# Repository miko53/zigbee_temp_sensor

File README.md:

# zigbee temperature sensor

This repository contains project about a temperature sensor based on Xbee device.
It will be coupled with the zigbee controler and the web_monitoring projets to resp. retrieve the value from the sensor 
and display thought a web site.

## Hardware part
The hardware folder groups schematics. it is based on a PIC device (PIC18LF2420) coupled with a XBee module (from Digi)
Temperature and Humidity sensor is a HYT221

## Firmware part
The folder contains source code to build the firmware for the PIC device.

## Features
 - read temperature and humidity around each minutes
 - read the battery voltage
 - PIC clock calibration
Most of 
 
##### Note:
 - acquisition period will be reviewed to improve consumption
 
autonomy test on going, with hourly reception of battery value and reception of temp/humidity each minutes
 - estimation: more than 6 months if I interpolate the current consumption.

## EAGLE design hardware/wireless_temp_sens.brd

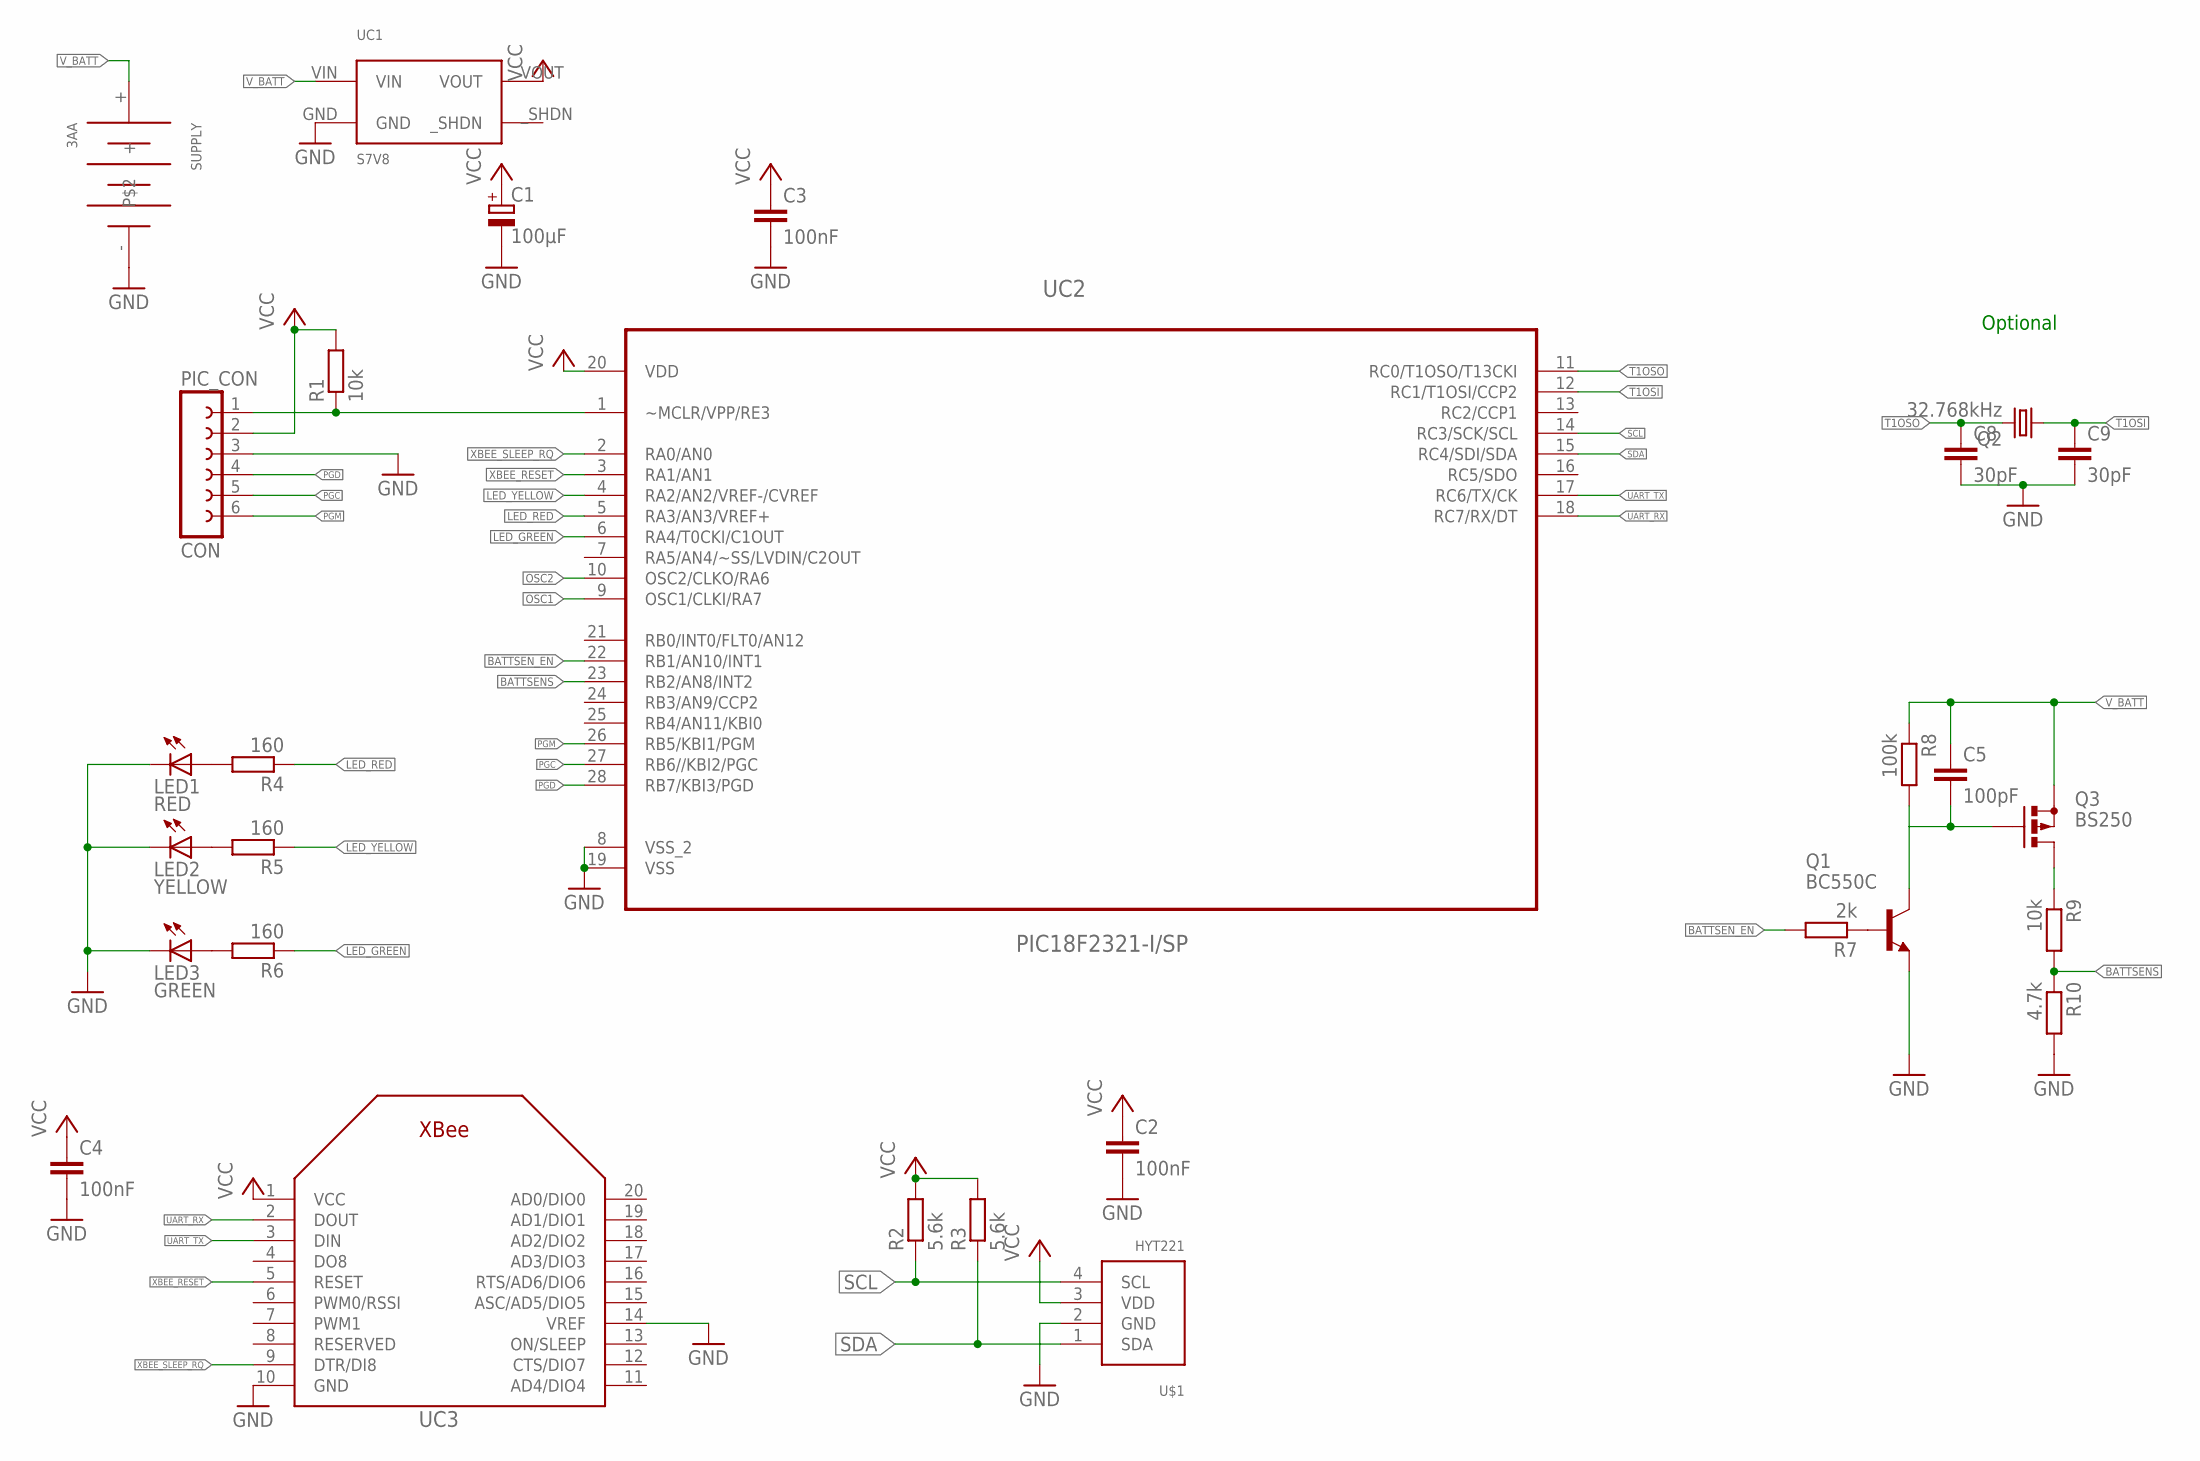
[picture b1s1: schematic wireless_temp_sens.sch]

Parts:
C1: 100µF; E2,5-6
C2, C3, C4: 100nF; C025-025X050
C5: 100pF; C025-025X050
C8, C9: 30pF; C025-024X044
CON: PIC_CON; FE06
LED1: RED; LED3MM
LED2: YELLOW; LED3MM
LED3: GREEN; LED3MM
Q1: BC550C; TO92-EBC
Q2: 32.768kHz; TC26H
Q3: BS250; SOT54E
R1, R9: 10k; 0204/7
R2, R3: 5.6k; 0204/7
R4, R5, R6: 160; 0204/7
R7: 2k; 0204/7
R8: 100k; 0204/7
R10: 4.7k; 0204/7
SUPPLY: 3AA; LR6-R6-R6P
U$1: HYT221HYT221-CON; HYT221-CON
UC1: S7V8; S7V8_P
UC2: PIC18F2321-I/SP; DIP254P762X508-28
UC3: XBEE

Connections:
BATTSENS: R9.2, R10.1, UC2.23 (RB2/AN8/INT2)
BATTSEN_EN: R7.2, UC2.22 (RB1/AN10/INT1)
GND: C1.-, C2.2, C3.2, C4.2, C8.2, C9.2, CON.3, LED1.K (C), LED2.K (C), LED3.K (C), Q1.E, R10.2, SUPPLY.-, U$1.2 (GND), UC1.GND, UC2.8 (VSS_2), UC2.19 (VSS), UC3.10 (GND), UC3.14 (VREF)
LED_GREEN: R6.1, UC2.6 (RA4/T0CKI/C1OUT)
LED_RED: R4.1, UC2.5 (RA3/AN3/VREF+)
LED_YELLOW: R5.1, UC2.4 (RA2/AN2/VREF-/CVREF)
unnamed: Q1.B, R7.1
unnamed: CON.1, R1.1, UC2.1 (~MCLR/VPP/RE3)
unnamed: Q3.D, R9.1
unnamed: C5.2, Q1.C, Q3.G, R8.2
unnamed: LED1.A, R4.2
unnamed: LED2.A, R5.2
unnamed: LED3.A, R6.2
OSC1: UC2.9 (OSC1/CLKI/RA7)
OSC2: UC2.10 (OSC2/CLKO/RA6)
PGC: CON.5, UC2.27 (RB6//KBI2/PGC)
PGD: CON.4, UC2.28 (RB7/KBI3/PGD)
PGM: CON.6, UC2.26 (RB5/KBI1/PGM)
SCL: R2.1, U$1.4 (SCL), UC2.14 (RC3/SCK/SCL)
SDA: R3.1, U$1.1 (SDA), UC2.15 (RC4/SDI/SDA)
T1OSI: C9.1, Q2.1, UC2.12 (RC1/T1OSI/CCP2)
T1OSO: C8.1, Q2.2, UC2.11 (RC0/T1OSO/T13CKI)
UART_RX: UC2.18 (RC7/RX/DT), UC3.2 (DOUT)
UART_TX: UC2.17 (RC6/TX/CK), UC3.3 (DIN)
VCC: C1.+, C2.1, C3.1, C4.1, CON.2, R1.2, R2.2, R3.2, U$1.3 (VDD), UC1.VOUT, UC2.20 (VDD), UC3.1 (VCC)
V_BATT: C5.1, Q3.S, R8.1, SUPPLY.+, UC1.VIN
XBEE_RESET: UC2.3 (RA1/AN1), UC3.5 (RESET)
XBEE_SLEEP_RQ: UC2.2 (RA0/AN0), UC3.9 (DTR/DI8)

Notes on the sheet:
Optional

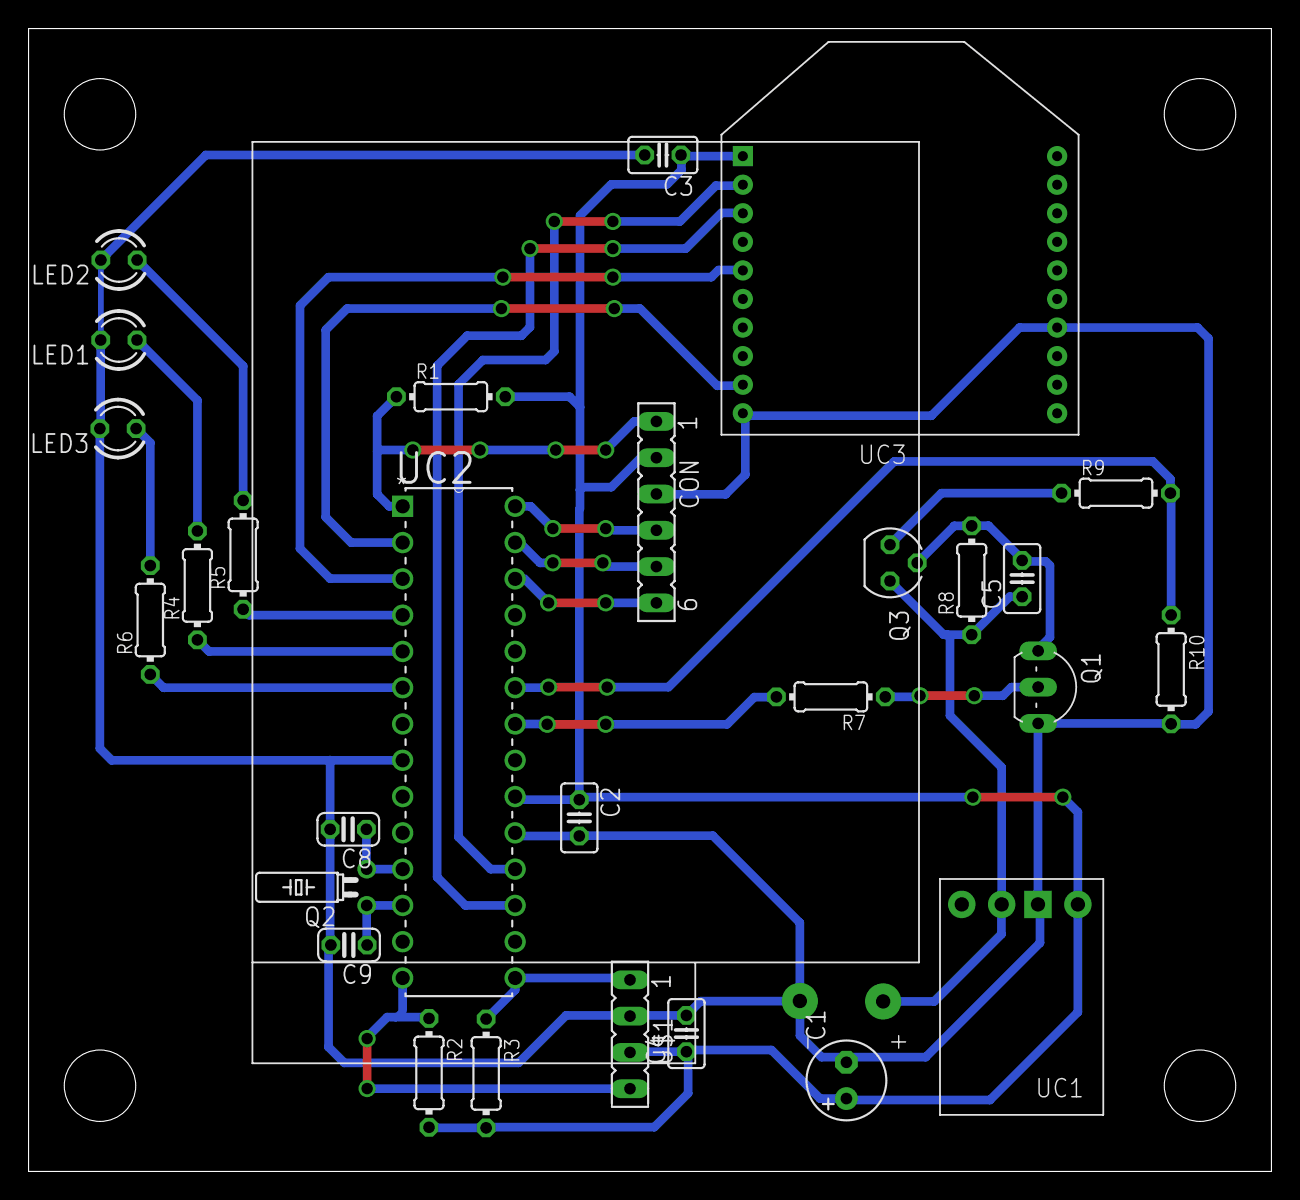
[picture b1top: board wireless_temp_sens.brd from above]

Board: 2 copper layers, 87.0 x 80.0 mm, 29 parts (0 on the bottom side), 26 nets.

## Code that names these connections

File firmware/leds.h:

/*
 * File:   leds.h
 * Author: mickael
 *
 * Created on 6 avril 2015, 12:30
 */

#ifndef LEDS_H
#define	LEDS_H

#ifdef	__cplusplus
extern "C" {
#endif

#define     LED_YELLOW      (0x04)
#define     LED_RED         (0x08)
#define     LED_GREEN       (0x10)

extern void leds_glitch(uint8_t leds);

#ifdef	__cplusplus
}
#endif

#endif	/* LEDS_H */

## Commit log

2015-07-18 initial
2015-07-19 update with sleep feature (zb sleep and pic sleep too), not yet finished
2015-07-25 update, remove leds ON/OFF and put glith for consumption
2015-09-13 move sw into firmware folder
2015-09-13 add first hardware version, not finished
2015-09-20 update board schema
2015-10-10 update schematic with G300 box
2015-10-11 add 2.54mm connector for I2C
2015-11-11 update schematcks (width, drill and voltage fct emplacement
2015-11-14 update resitor value or A/D conversion and update brd to remove some vias
2016-02-12 reorganize folder to insert web and controler app
2016-02-12 undo
2016-04-12 update with 6dec version with new micro
2016-05-05 add sleep mode with battery each 5min, + sleep mode when attempt to join
2016-05-16 some update on firmware code, put in idle in I2C operation, set at output some I/O, remove unnecessary loop and set ZB in sleep more long time
2016-06-04 fix consumption issue, the XBee module is not put in SLEEP state (wrong PIN used before)
2016-07-02 add clean up of code + rise the transmission time
2016-08-15 astylized
2016-08-15 clean up and add result of compilation + Makefile
2016-08-15 add waiting for ack from network controler, split main state into two states (more readable)
2016-08-28 add filering + increase wait time for ack for zigbee
2016-09-10 rework temperature,humidity formula. no more reset on Xbee disassociated, fix bug on Xbee sleep and Xbee status. Add more timeout for ack
2016-09-11 modify RED led by GREEN led at start-up, add laucnh-acq on reset
2016-09-17 add compilation items
2016-12-16 add under compilation flag possibility to send debug frame, simplificate management when XBEE lost network, check battery for 4 hours instead of one.
